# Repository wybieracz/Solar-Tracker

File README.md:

# Solar-Tracker
The aim of the project was to design and build a model of a mobile platform for a photovoltaic panel. The platform moves in two axes: horizontal and vertical, adjusting its position to make the most effective use of the sunlight falling on the panel. The program that determines the best position of the platform uses data provided by the light detection module connected to the microcontroller. The platform is moved by two servos controlled by the microcontroller.
## General information
* Model of a platform for a photovoltaic panel
* Rotation in vertical and horizontal axies
* Automatically follows the light
## Technologies used
* C
* Autodesk EAGLE
* Arduino Nano
## Schematic

## Components description
* Arduino Nano - microcontroller.
* J1 - Power module with DC 2.1/5.5mm socket.
* LIGHT_DETECTOR - connector to the light detection sensor. Connected to Arduino Nano analog pins A0 - A3 and 5V0.
* SERVO_1, SERVO_2 - connectors to the servos. Connected to Arduino Nano digital pins D9, D10, 5V0 and GND.
* R0 - R3 - 10k resistors necessary to read data from the light detection system.
* C1 - Electrolytic capacitor 100u which guarantees stable operation of the whole system.
* C2 - ceramic capacitor 100n guaranteeing stable operation of the microprocessor.
* C3, C5 - ceramic capacitors 100n guaranteeing stable operation of the servomechanisms.
* C4, C6 - 100u electrolytic capacitors guaranteeing stable operation of servos.
## Photos

## Video
* https://youtu.be/d5iRpRQZef4
## Links
* https://docs.arduino.cc/hardware/nano
* https://www.arduino.cc/reference/en/
* https://www.thingiverse.com/thing:708819
* https://diyi0t.com/arduino-nano-tutorial/

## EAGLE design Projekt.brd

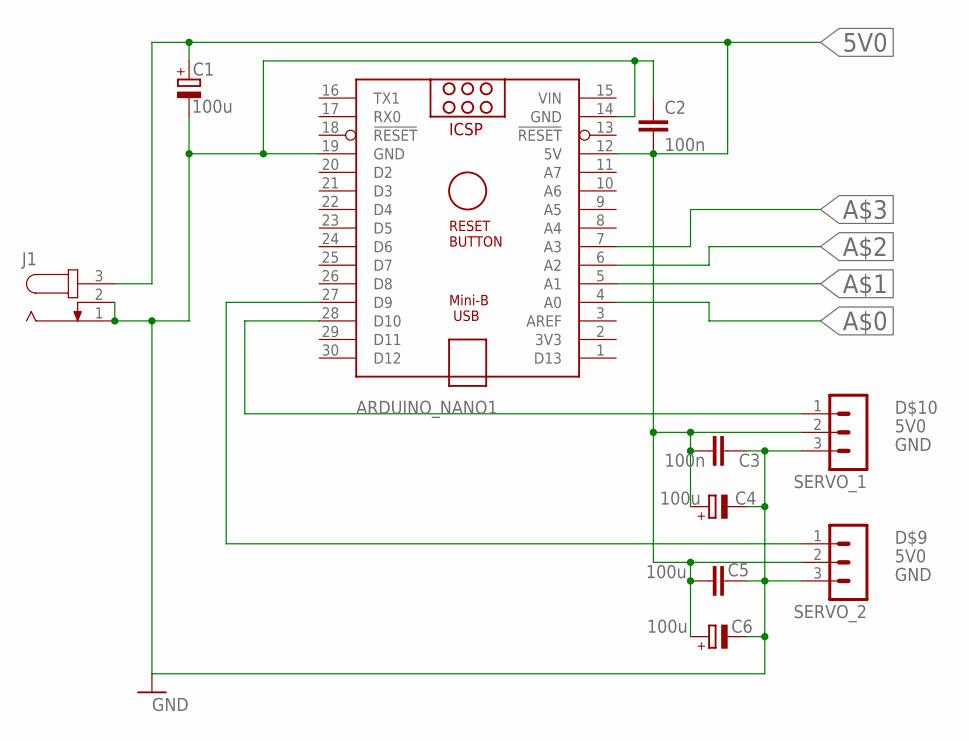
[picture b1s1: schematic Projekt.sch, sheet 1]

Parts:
ARDUINO_NANO1: ARDUINO_NANO
C1, C4, C6: 100u; E2,5-6E
C2, C3: 100n; C050-024X044
C5: 100u; C050-024X044
J1: JACK-PLUG0; SPC4077
SERVO_1, SERVO_2: MA03-1

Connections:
5V0: ARDUINO_NANO1.12 (5V), C1.+, C2.2, C3.2, C4.+, C5.2, C6.+, J1.3, SERVO_1.2, SERVO_2.2; also elsewhere on the board
A$0: ARDUINO_NANO1.4 (A0); also elsewhere on the board
A$1: ARDUINO_NANO1.5 (A1); also elsewhere on the board
A$2: ARDUINO_NANO1.6 (A2); also elsewhere on the board
A$3: ARDUINO_NANO1.7 (A3); also elsewhere on the board
D$9: ARDUINO_NANO1.27 (D9), SERVO_2.1
D$10: ARDUINO_NANO1.28 (D10), SERVO_1.1
GND: ARDUINO_NANO1.14 (GND), ARDUINO_NANO1.19 (GND), C1.-, C2.1, C3.1, C4.-, C5.1, C6.-, J1.1, J1.2, SERVO_1.3, SERVO_2.3; also elsewhere on the board
VIN: ARDUINO_NANO1.15 (VIN)

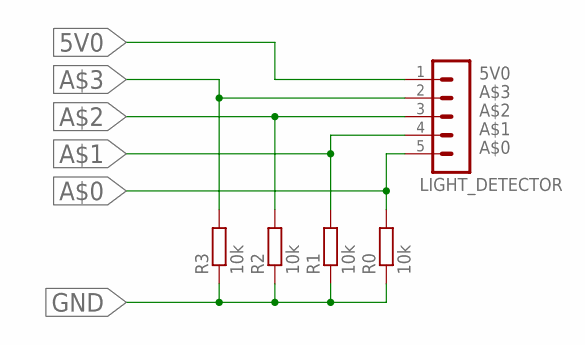
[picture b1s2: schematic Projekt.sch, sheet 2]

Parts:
LIGHT_DETECTOR: MA05-1
R0, R1, R2, R3: 10k; 0207/10

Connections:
5V0: LIGHT_DETECTOR.1; also elsewhere on the board
A$0: LIGHT_DETECTOR.5, R0.2; also elsewhere on the board
A$1: LIGHT_DETECTOR.4, R1.2; also elsewhere on the board
A$2: LIGHT_DETECTOR.3, R2.2; also elsewhere on the board
A$3: LIGHT_DETECTOR.2, R3.2; also elsewhere on the board
GND: R0.1, R1.1, R2.1, R3.1; also elsewhere on the board

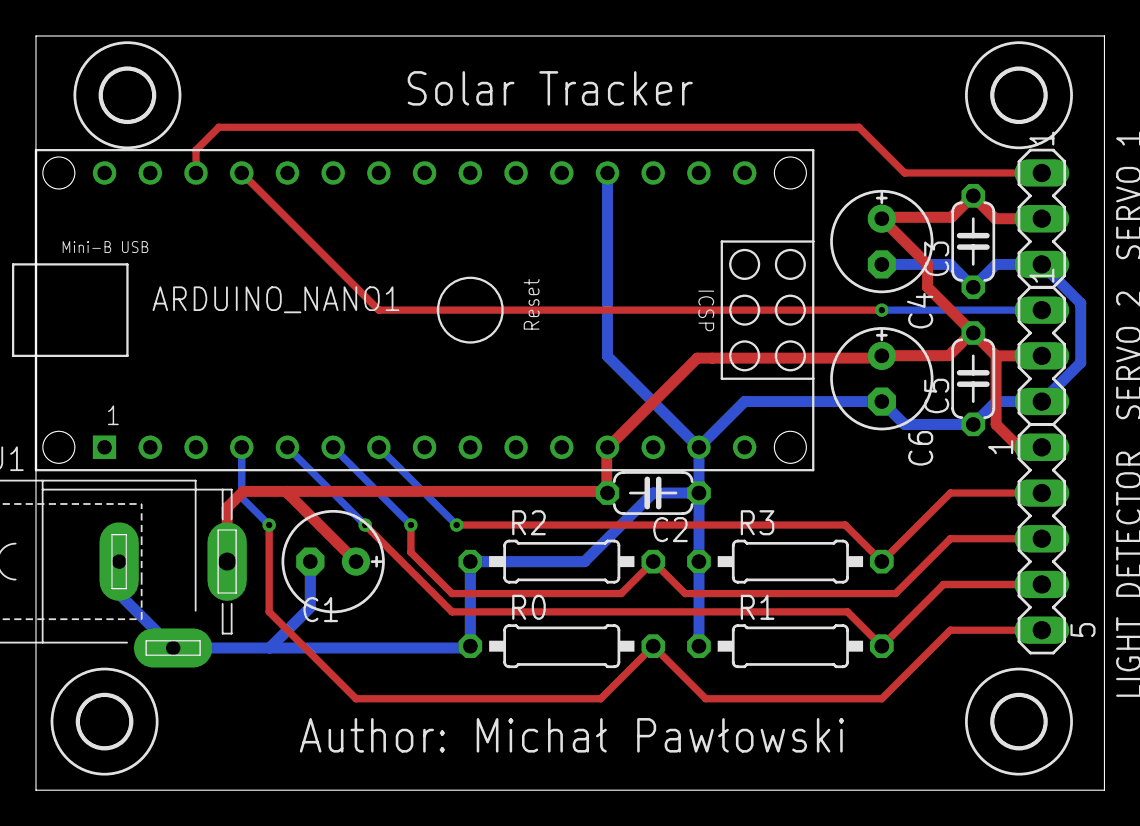
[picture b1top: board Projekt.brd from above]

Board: 2 copper layers, 59.4 x 41.9 mm, 19 parts (0 on the bottom side), 8 nets.

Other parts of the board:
U$1, U$2, U$3, U$4: 2,8

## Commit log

2022-03-17 feat: platform driver and documentation
2022-03-17 feat: readme update
2022-03-17 feat: readme links update
2022-03-17 feat: readme yt link
